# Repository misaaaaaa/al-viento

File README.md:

# al-viento
pcb para máquina generadora de campos intensivos

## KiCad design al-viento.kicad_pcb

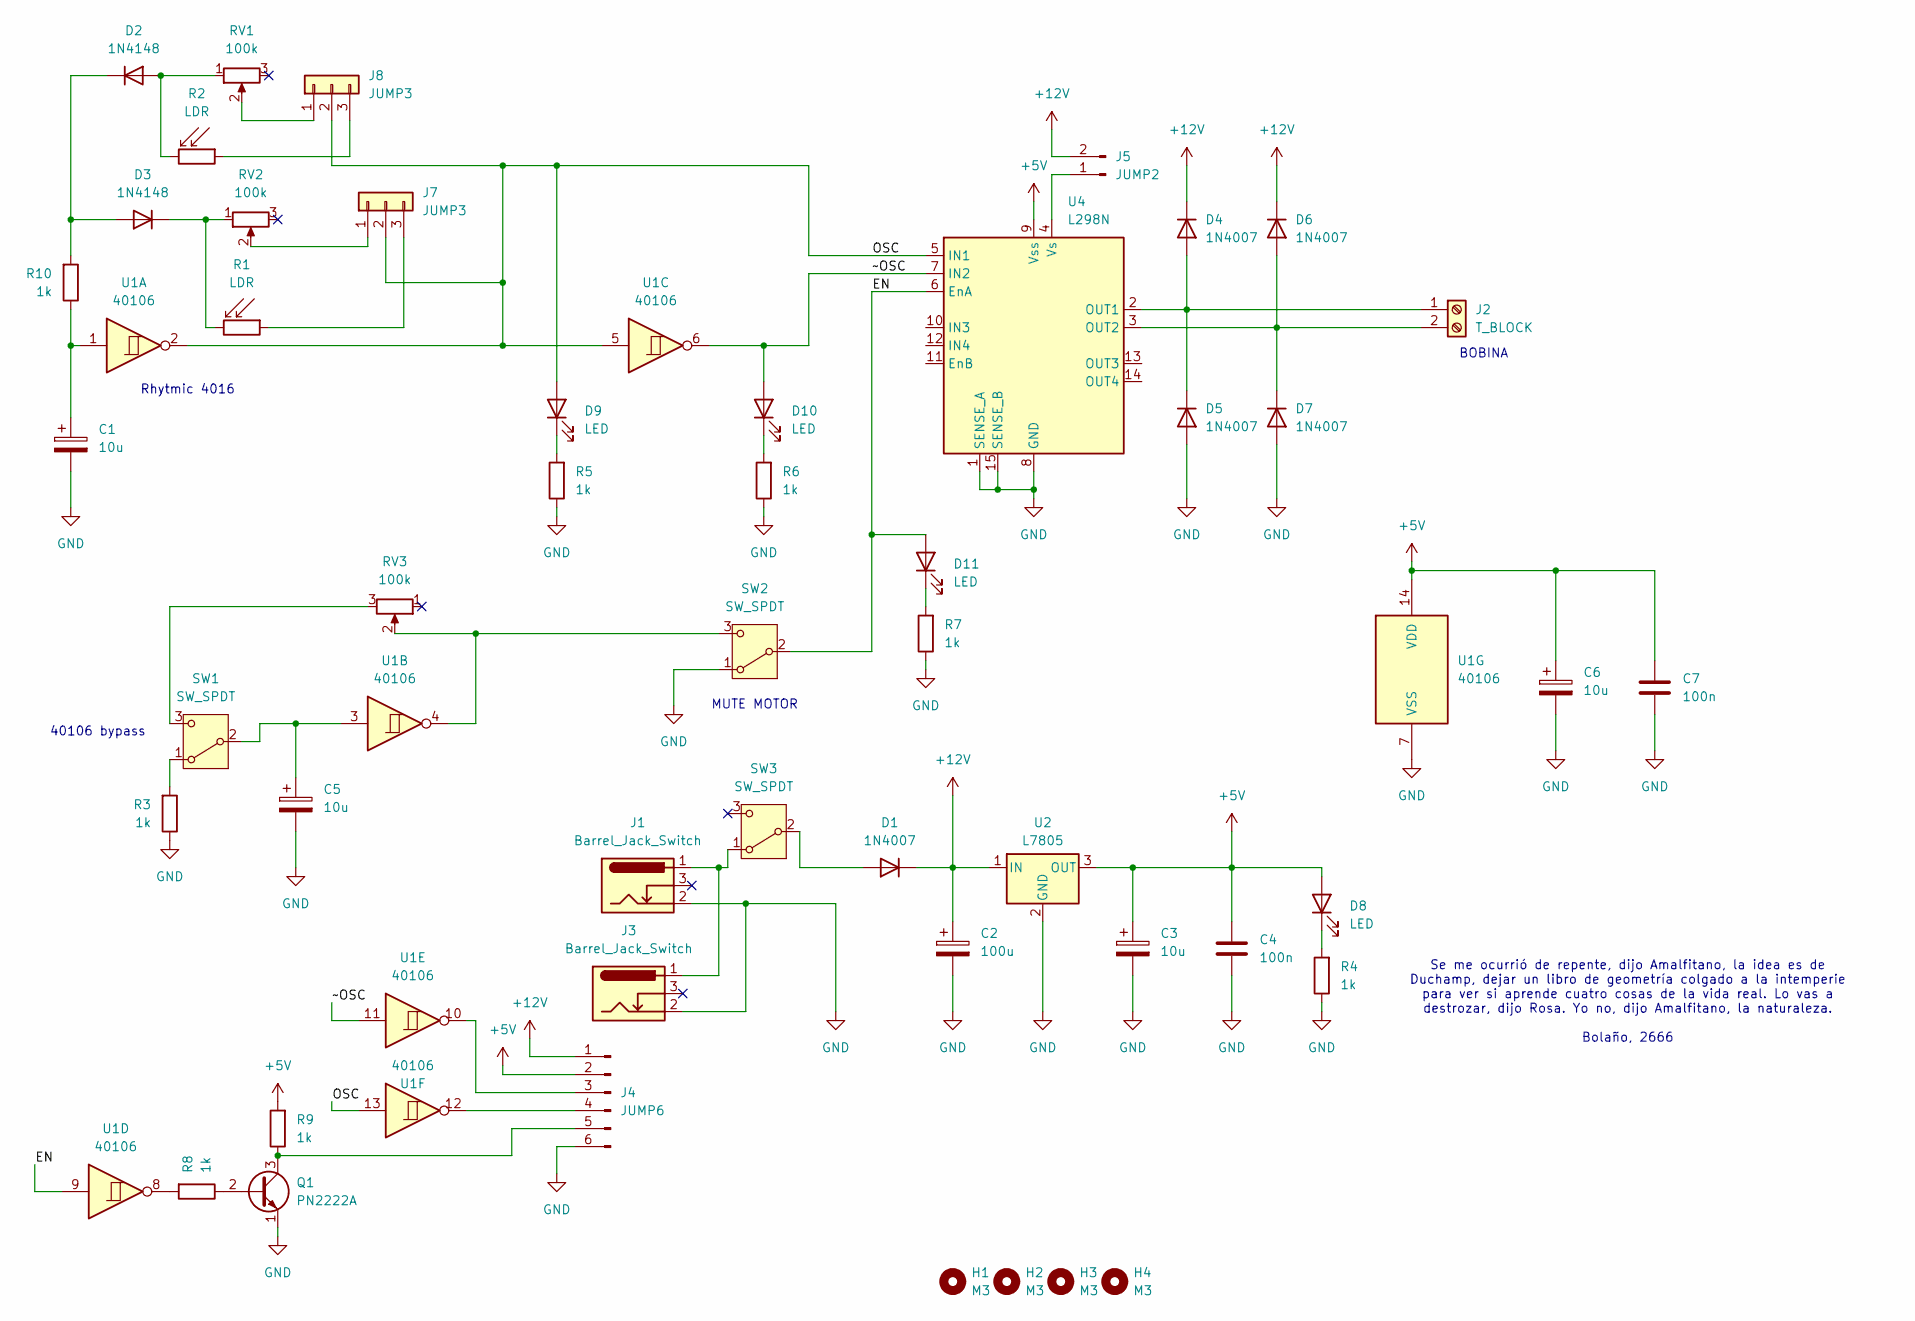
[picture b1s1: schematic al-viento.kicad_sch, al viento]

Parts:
C1, C3, C5, C6: 10u; CP_Radial_D4.0mm_P2.00mm
C2: 100u; CP_Radial_D8.0mm_P3.80mm
C4, C7: 100n; C_Disc_D5.0mm_W2.5mm_P2.50mm
D1, D4, D5, D6, D7: 1N4007; D_DO-41_SOD81_P10.16mm_Horizontal
D2, D3: 1N4148; D_DO-35_SOD27_P7.62mm_Horizontal
D8, D9, D10, D11: LED; LED_PCBasDiffuser
H1, H2, H3, H4: M3; MountingHole_3.2mm_M3
J1, J3: Barrel_Jack_Switch; BarrelJack_Horizontal
J2: T_BLOCK; TerminalBlock_Phoenix_PT-1,5-2-5.0-H_1x02_P5.00mm_Horizontal
J4: JUMP6; PinHeader_1x06_P2.54mm_Vertical
J5: JUMP2; PinHeader_1x02_P2.54mm_Vertical
J7, J8: JUMP3; PinHeader_1x03_P2.54mm_Vertical
Q1: PN2222A; TO-92_Inline_Wide
R1, R2: LDR; R_LDR_5.0x4.1mm_P3mm_Vertical
R3, R4, R5, R6, R7, R8, R9, R10: 1k; R_Axial_DIN0207_L6.3mm_D2.5mm_P10.16mm_Horizontal
RV1, RV2, RV3: 100k; Potentiometer_Bourns_PTV09A-1_Single_Vertical
SW1, SW2, SW3: SW_SPDT; SPST_ALIEXPRESS
U1: 40106; DIP-14_W7.62mm_LongPads
U2: L7805; TO-252-2
U4: L298N; TO-220-15_P2.54x5.08mm_StaggerOdd_Lead4.58mm_Vertical

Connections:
+5V: C3.1, C4.1, C6.1, C7.1, D8.2 (A), J4.2, R9.2, U1.14 (VDD), U2.3 (OUT), U4.9 (Vss)
+12V: C2.1, D1.1 (K), D4.1 (K), D6.1 (K), J4.1, J5.2, U2.1 (IN)
/EN: D11.2 (A), SW2.2 (B), U1.9, U4.6 (EnA)
/OSC: D9.2 (A), J7.2, J8.2, U1.2, U1.5, U1.13, U4.5 (IN1)
/~OSC: D10.2 (A), U1.6, U1.11, U4.7 (IN2)
GND: C1.2, C2.2, C3.2, C4.2, C5.2, C6.2, C7.2, D5.2 (A), D7.2 (A), J1.2, J3.2, J4.6, Q1.1 (E), R3.1, R4.1, R5.1, R6.1, R7.1, SW2.1 (A), U1.7 (VSS), U2.2 (GND), U4.1 (SENSE_A), U4.8 (GND), U4.15 (SENSE_B)
unnamed: C1.1, R10.1, U1.1
unnamed: D1.2 (A), SW3.2 (B)
unnamed: D2.2 (A), R2.2, RV1.1
unnamed: D2.1 (K), D3.2 (A), R10.2
unnamed: D3.1 (K), R1.2, RV2.1
unnamed: D4.2 (A), D5.1 (K), J2.1, U4.2 (OUT1)
unnamed: D6.2 (A), D7.1 (K), J2.2, U4.3 (OUT2)
unnamed: D8.1 (K), R4.2
unnamed: D9.1 (K), R5.2
unnamed: D10.1 (K), R6.2
unnamed: D11.1 (K), R7.2
unnamed: J4.3, U1.10
unnamed: J4.4, U1.12
unnamed: J4.5, Q1.3 (C), R9.1
unnamed: J5.1, U4.4 (Vs)
unnamed: J7.1, RV2.2
unnamed: J7.3, R1.1
unnamed: J8.1, RV1.2
unnamed: J8.3, R2.1
unnamed: Q1.2 (B), R8.1
unnamed: R8.2, U1.8
unnamed: R3.2, SW1.1 (A)
unnamed: C5.1, SW1.2 (B), U1.3
unnamed: RV3.3, SW1.3 (C)
unnamed: RV3.2, SW2.3 (C), U1.4
unnamed: J1.1, J3.1, SW3.1 (A)

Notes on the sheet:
40106 bypass
BOBINA
Rhytmic 4016
MUTE MOTOR
Se me ocurrió de repente, dijo Amalfitano, la idea es de Duchamp, dejar un libro de geometría colgado a la intemperie para ver si aprende cuatro cosas de la vida real. Lo vas a destrozar, dijo Rosa. Yo no, dijo Amalfitano, la naturaleza. Bolaño, 2666

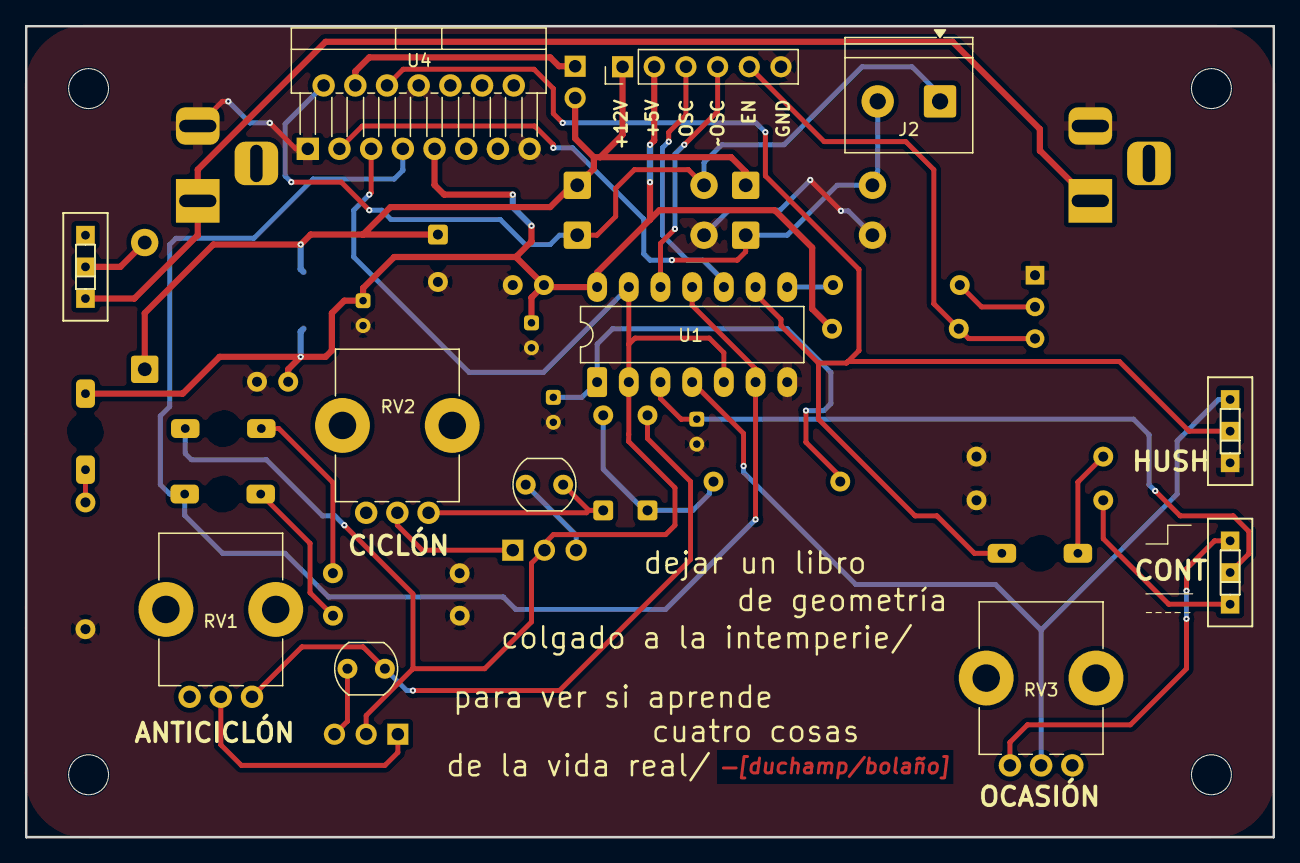
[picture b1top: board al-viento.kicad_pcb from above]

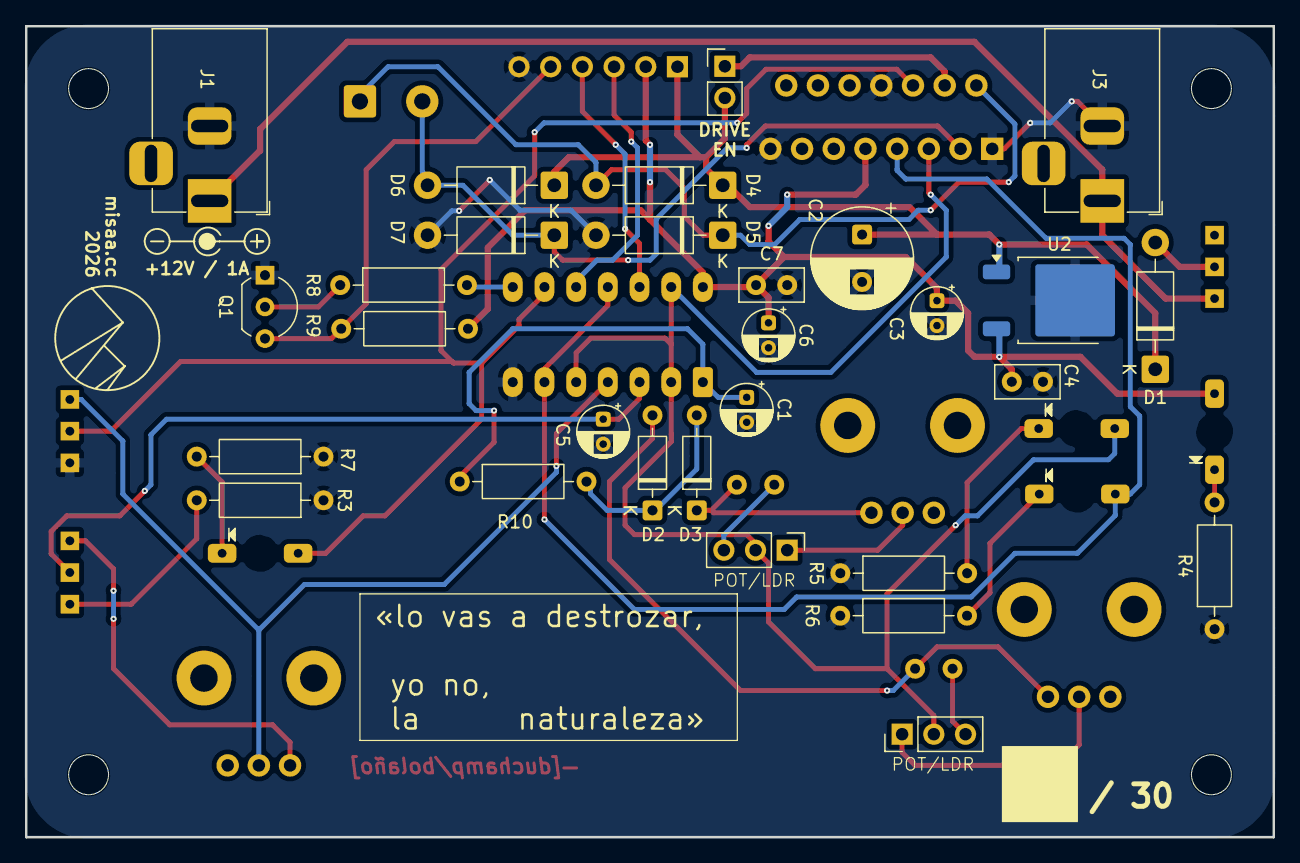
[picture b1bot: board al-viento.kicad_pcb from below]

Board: 2 copper layers, 100.0 x 65.0 mm, 49 parts (29 on the bottom side), 32 nets.

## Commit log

2026-05-21 añadidos archivos
2026-06-17 añadido sch y csv
2026-06-17 añadido csv
